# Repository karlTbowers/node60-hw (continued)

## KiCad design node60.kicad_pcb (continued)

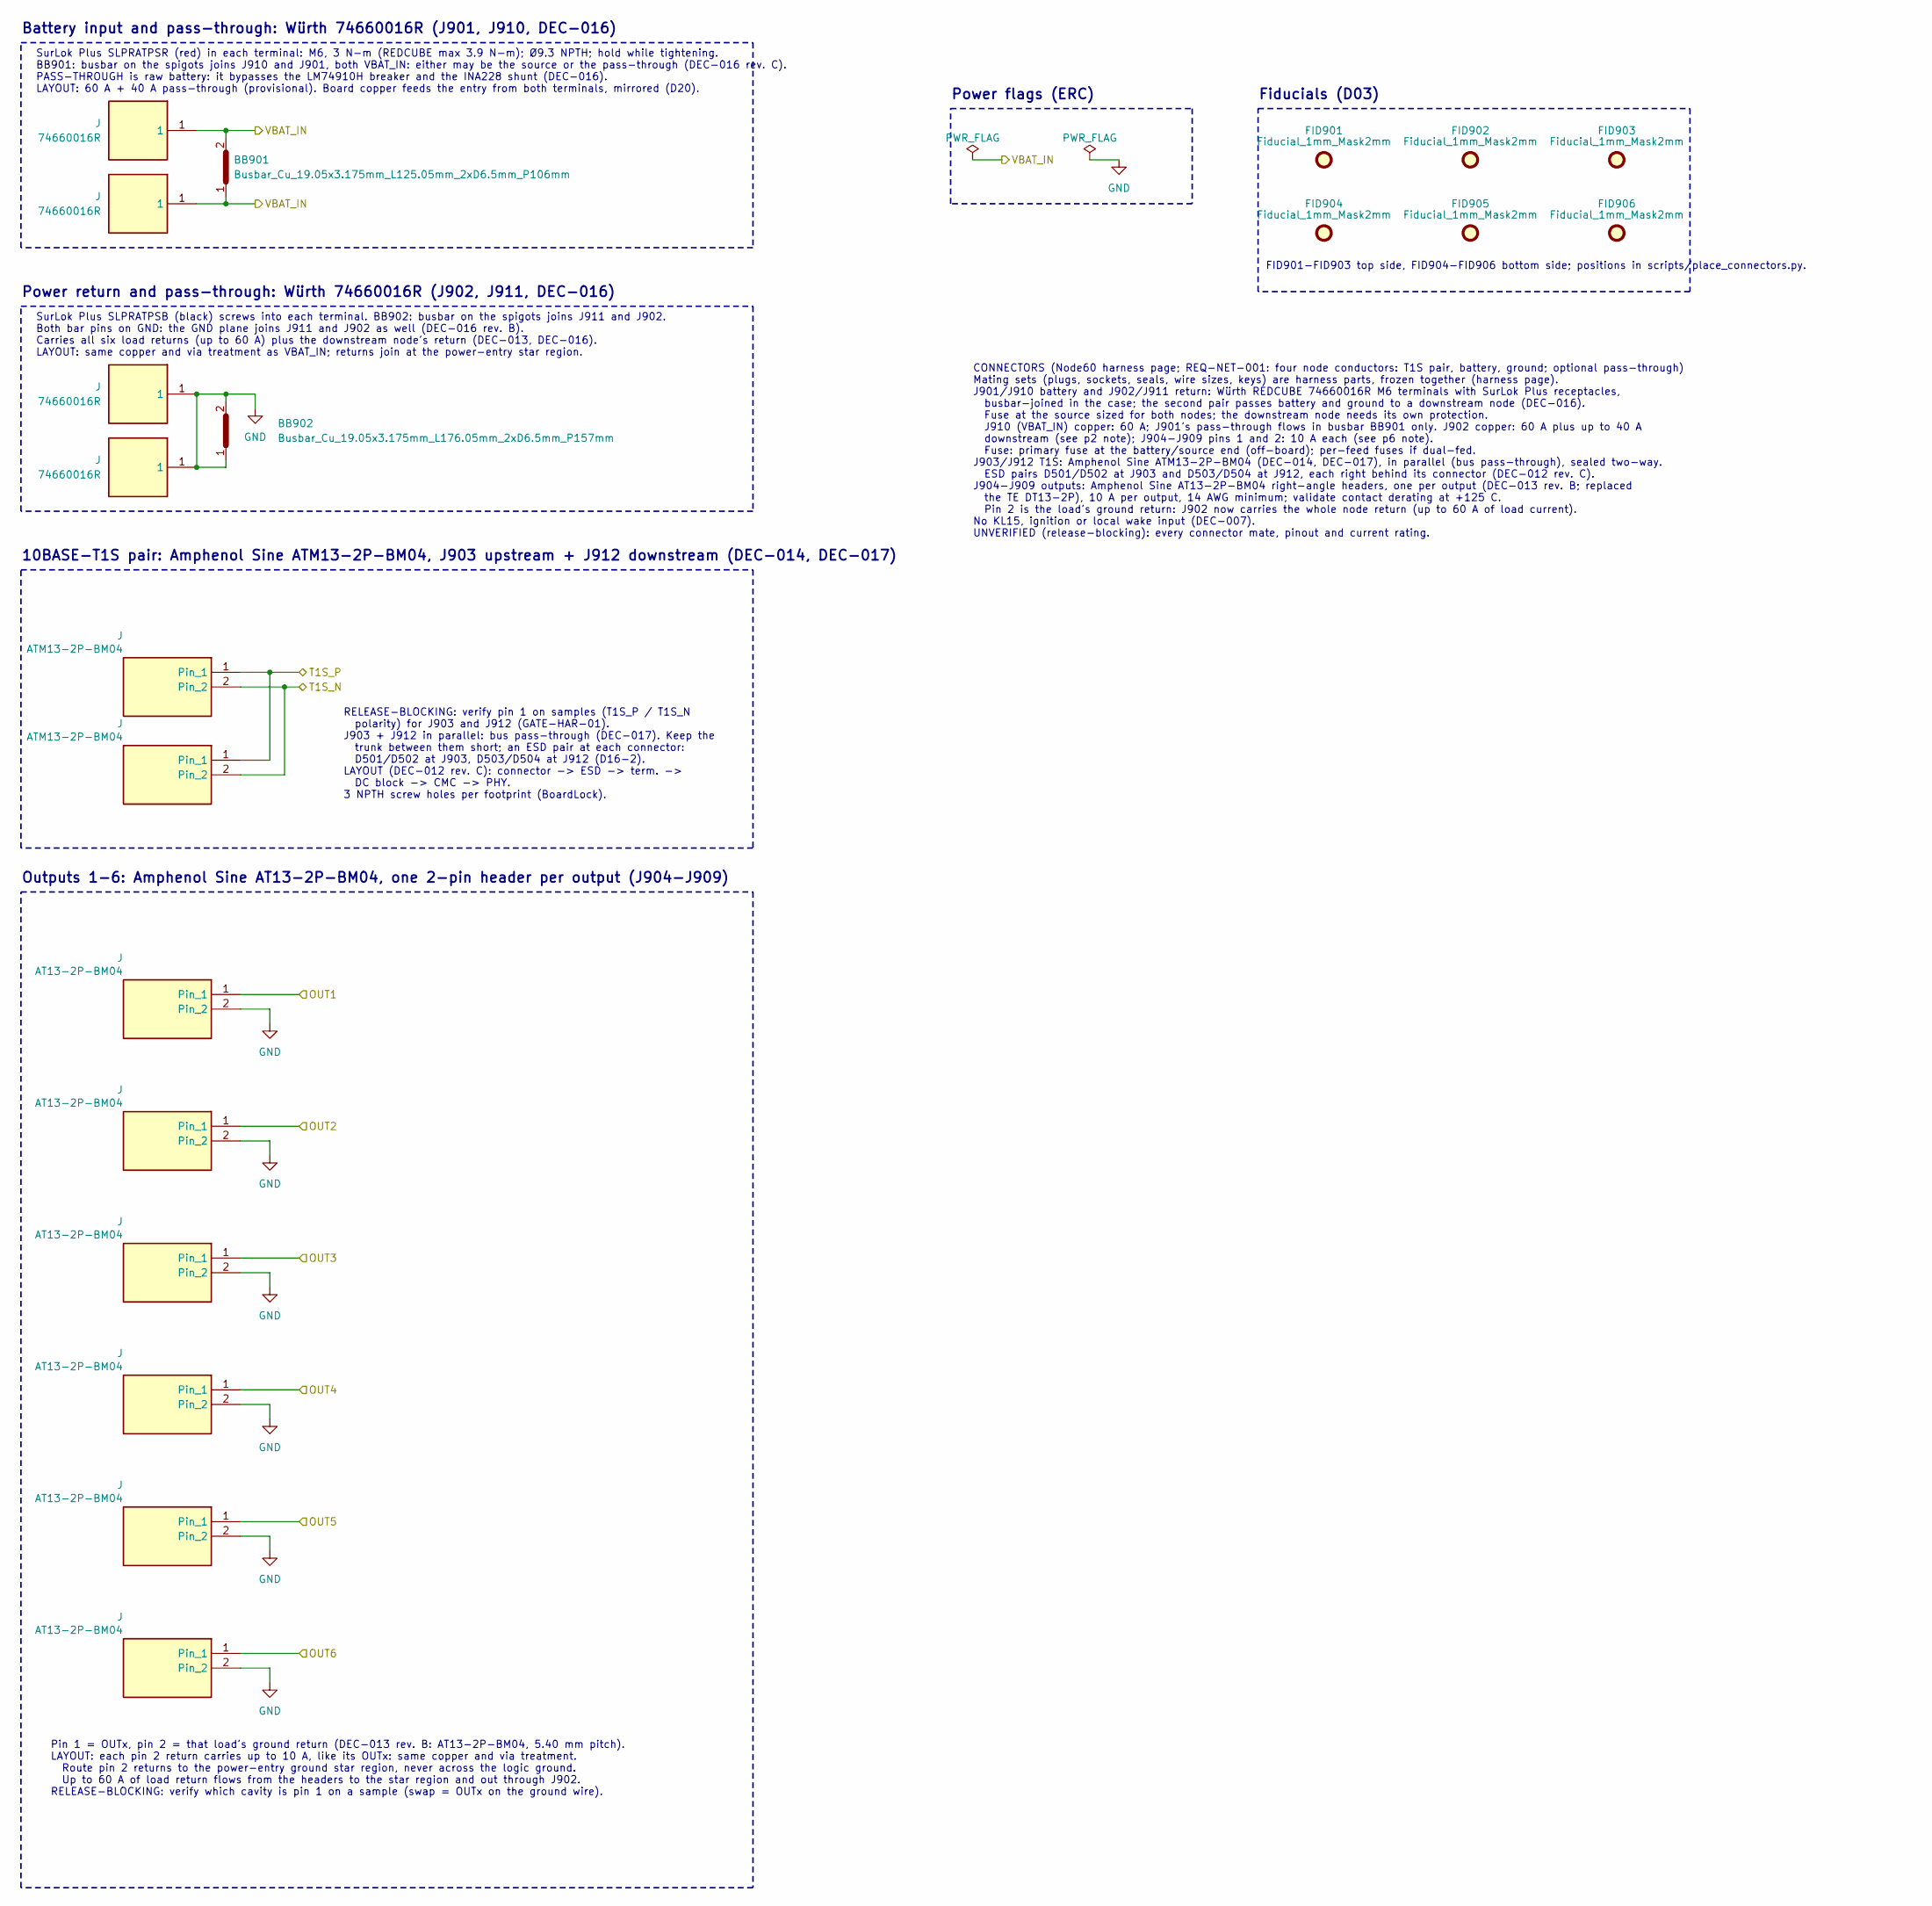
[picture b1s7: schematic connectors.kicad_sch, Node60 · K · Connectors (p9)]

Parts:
BB901: Busbar_Cu_19.05x3.175mm_L125.05mm_2xD6.5mm_P106mm; MPN Busbar_Cu_19.05x3.175mm_L125.05mm_2xD6.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
BB902: Busbar_Cu_19.05x3.175mm_L176.05mm_2xD6.5mm_P157mm; MPN Busbar_Cu_19.05x3.175mm_L176.05mm_2xD6.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
FID901, FID902, FID903, FID904, FID905, FID906: Fiducial_1mm_Mask2mm; MPN Fiducial_1mm_Mask2mm
J: ATM13-2P-BM04; Amphenol_ATM13-2P-BMxx_1x02_P4.20mm_Horizontal; MPN ATM13-2P-BM04; DigiKey_PN 889-3357-ND

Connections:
/VBAT_IN: BB901.1, BB901.2; also elsewhere on the board
GND: BB902.1, BB902.2; also elsewhere on the board

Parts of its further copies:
J903, J912: ATM13-2P-BM04; Amphenol_ATM13-2P-BMxx_1x02_P4.20mm_Horizontal; MPN ATM13-2P-BM04; DigiKey_PN 889-3357-ND

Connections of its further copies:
/T1S_N: J903.2, J912.2; also elsewhere on the board
/T1S_P: J903.1, J912.1; also elsewhere on the board

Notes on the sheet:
Battery input and pass-through: Würth 74660016R (J901, J910, DEC-016)
Power return and pass-through: Würth 74660016R (J902, J911, DEC-016)
10BASE-T1S pair: Amphenol Sine ATM13-2P-BM04, J903 upstream + J912 downstream (DEC-014, DEC-017)
RELEASE-BLOCKING: verify pin 1 on samples (T1S_P / T1S_N polarity) for J903 and J912 (GATE-HAR-01). J903 + J912 in parallel: bus pass-through (DEC-017). Keep the trunk between them short; an ESD pair at each connector: D501/D502 at J903, D503/D504 at J912 (D16-2). LAYOUT (DEC-012 rev. C): connector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
Outputs 1-6: Amphenol Sine AT13-2P-BM04, one 2-pin header per output (J904-J909)
Pin 1 = OUTx, pin 2 = that load's ground return (DEC-013 rev. B: AT13-2P-BM04, 5.40 mm pitch). LAYOUT: each pin 2 return carries up to 10 A, like its OUTx: same copper and via treatment. Route pin 2 returns to the power-entry ground star region, never across the logic ground. Up to 60 A of load ret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
Power flags (ERC)
CONNECTORS (Node60 harness page; REQ-NET-001: four node conductors: T1S pair, battery, ground; optional pass-through) Mating sets (plugs, sockets, seals, wire sizes, keys) are harness parts, frozen together (harness page). J901/J910 battery and J902/J911 return: Würth REDCUBE 74660016R M6 terminals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
SurLok Plus SLPRATPSR (red) in each terminal: M6, 3 N-m (REDCUBE max 3.9 N-m); Ø9.3 NPTH; hold while tightening. BB901: busbar on the spigots joins J910 and J901, both VBAT_IN: either may be the source or the pass-through (DEC-016 rev. C). PASS-THROUGH is raw battery: it bypasses the LM74910H break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
Fiducials (D03)
FID901-FID903 top side, FID904-FID906 bottom side; positions in scripts/place_connectors.py.
SurLok Plus SLPRATPSB (black) screws into each terminal. BB902: busbar on the spigots joins J911 and J902. Both bar pins on GND: the GND plane joins J911 and J902 as well (DEC-016 rev. B). Carries all six load returns (up to 60 A) plus the downstream node's return (DEC-013, DEC-016). LAYOUT: same c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

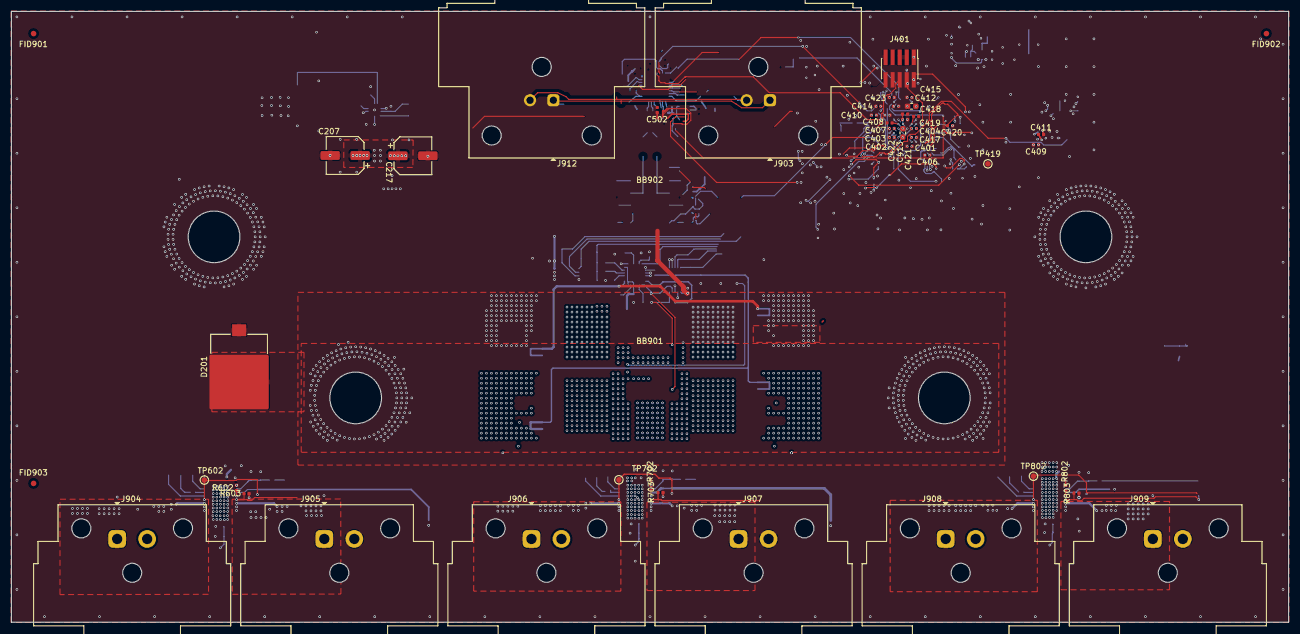
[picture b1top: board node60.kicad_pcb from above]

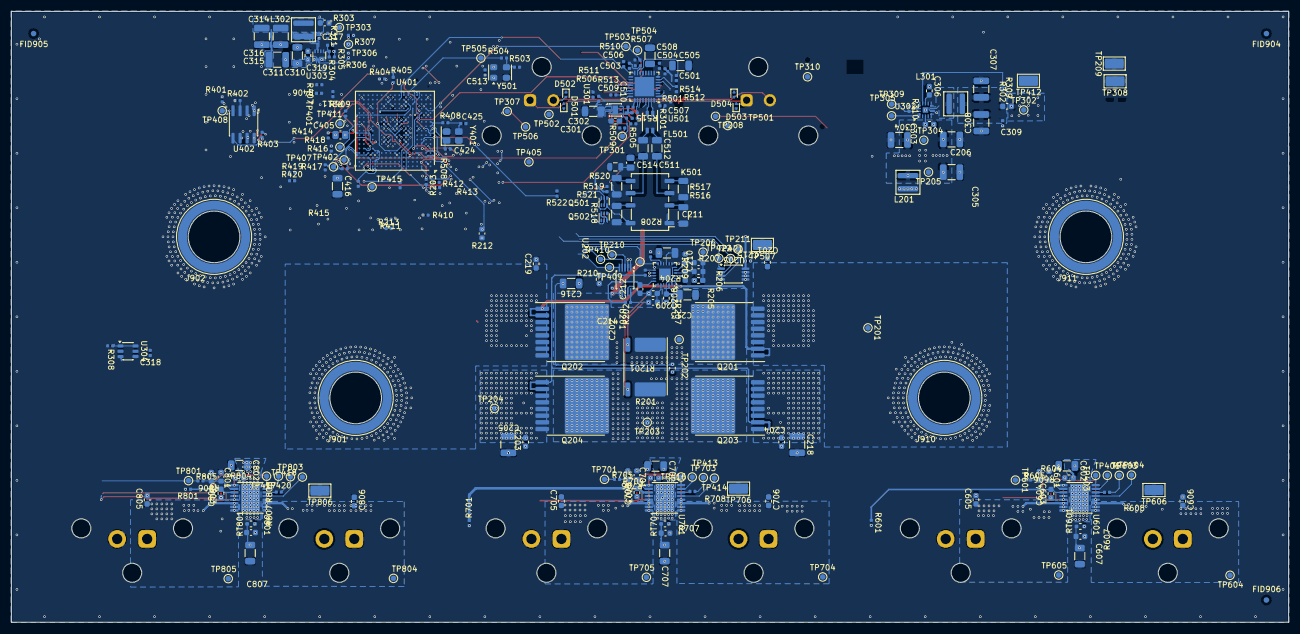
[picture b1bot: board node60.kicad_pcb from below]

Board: 6 copper layers, 230.0 x 110.0 mm, 309 parts (260 on the bottom side), 142 nets.

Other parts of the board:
C602, C702, C802: 1uF; C_1206_3216Metric
C603, C703, C803: 470nF; C_0603_1608Metric
C604, C704, C804: 4.7nF; C_0603_1608Metric
J901, J902, J910, J911: 74660016R; Wuerth_REDCUBE-SMT_WP-SMRT_74660016
J904, J905, J906, J907, J908, J909: AT13-2P-BM04; Amphenol_AT13-2P-BMxx_1x02_P5.40mm_Horizontal
R602, R603, R606, R702, R703, R706, R802, R803, R806: 10k; R_0402_1005Metric
R604, R704, R804: 4.7k; R_0402_1005Metric
R605, R705, R805: 698R; R_0603_1608Metric
R607, R707, R807: 10k; R_0603_1608Metric
R608, R708, R808: 33R; R_0402_1005Metric
TP606, TP706, TP806: S1751-46R; TestPoint_Harwin_S1751

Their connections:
3V3_MAIN: R607.1, R707.1, R807.1; also elsewhere on the board
/NTC_SW1: R607.2; also elsewhere on the board
/NTC_SW2: R707.2; also elsewhere on the board
/NTC_SW3: R807.2; also elsewhere on the board
/OUT1: J904.1; also elsewhere on the board
/OUT2: J905.1; also elsewhere on the board
/OUT3: J906.1; also elsewhere on the board
/OUT4: J907.1; also elsewhere on the board
/OUT5: J908.1; also elsewhere on the board
/OUT6: J909.1; also elsewhere on the board
/Outputs 1-2/SW_DI: R602.1; also elsewhere on the board
/Outputs 1-2/SW_SDO: R608.1; also elsewhere on the board
/Outputs 1-2/SW_SNS: C604.1, R605.1, R606.1; also elsewhere on the board
/Outputs 1-2/SW_VDD: C603.1, R604.2; also elsewhere on the board
/Outputs 3-4/SW_DI: R702.1; also elsewhere on the board
/Outputs 3-4/SW_SDO: R708.1; also elsewhere on the board
/Outputs 3-4/SW_SNS: C704.1, R705.1, R706.1; also elsewhere on the board
/Outputs 3-4/SW_VDD: C703.1, R704.2; also elsewhere on the board
/Outputs 5-6/SW_DI: R802.1; also elsewhere on the board
/Outputs 5-6/SW_SDO: R808.1; also elsewhere on the board
/Outputs 5-6/SW_SNS: C804.1, R805.1, R806.1; also elsewhere on the board
/Outputs 5-6/SW_VDD: C803.1, R804.2; also elsewhere on the board
/SPI3_SWITCH3_MISO: R808.2; also elsewhere on the board
/SPI4_SWITCH1_MISO: R608.2; also elsewhere on the board
/SPI5_SWITCH2_MISO: R708.2; also elsewhere on the board
/SW1_FLT_L: R604.1; also elsewhere on the board
/SW1_SNS: R606.2; also elsewhere on the board
/SW2_FLT_L: R704.1; also elsewhere on the board
/SW2_SNS: R706.2; also elsewhere on the board
/SW3_FLT_L: R804.1; also elsewhere on the board
/SW3_SNS: R806.2; also elsewhere on the board
/SW_LHI: R603.1, R703.1, R803.1; also elsewhere on the board
/VBAT_IN: J901.1 (1_1), J910.1 (1_1); also elsewhere on the board
GND: C602.2, C603.2, C604.2, C702.2, C703.2, C704.2, C802.2, C803.2, C804.2, J902.1 (1_1), J904.2, J905.2, J906.2, J907.2, J908.2, J909.2, J911.1 (1_1), R602.2, R603.2, R605.2, R702.2, R703.2, R705.2, R802.2, R803.2, R805.2, TP606.1 (1_1), TP706.1 (1_1), TP806.1 (1_1); also elsewhere on the board
VBAT_PROT: C602.1, C702.1, C802.1; also elsewhere on the board
